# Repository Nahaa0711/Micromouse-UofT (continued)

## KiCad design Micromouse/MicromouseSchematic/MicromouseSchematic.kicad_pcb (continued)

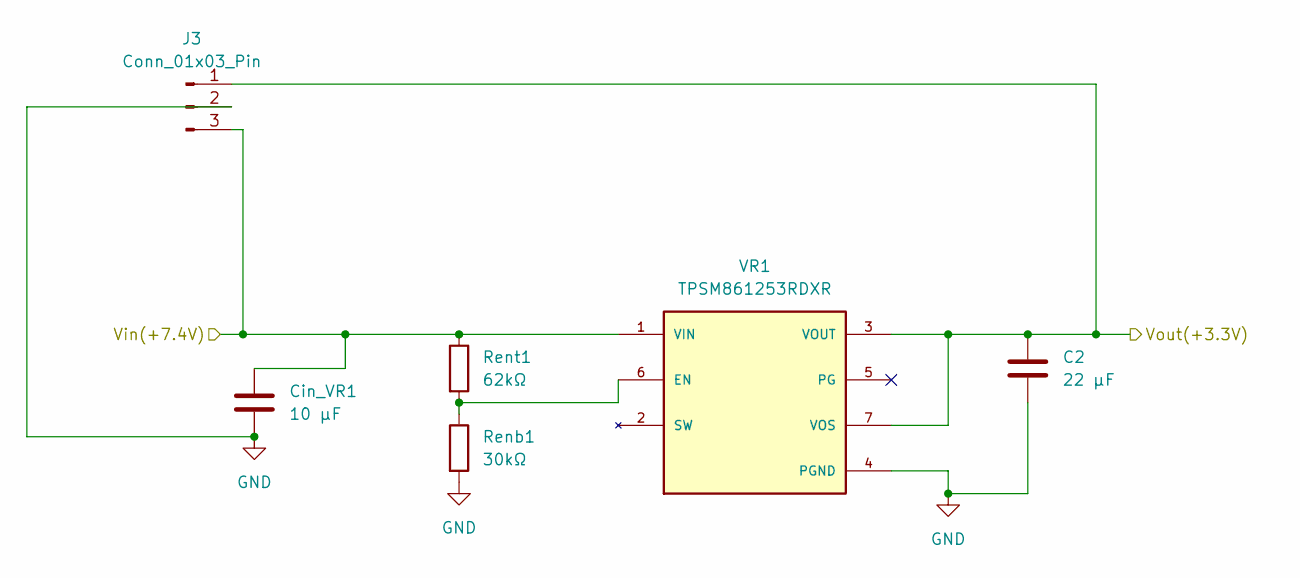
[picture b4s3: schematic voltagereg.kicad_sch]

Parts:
C2: 22 µF; C_0402_1005Metric
Cin_VR1: 10 µF; C_0402_1005Metric
J3: Conn_01x03_Pin; JST_ZH_B3B-ZR_1x03_P1.50mm_Vertical
Renb1: 30kΩ; R_0603_1608Metric
Rent1: 62kΩ; R_0603_1608Metric
VR1: TPSM861253RDXR; PARTREV B

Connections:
+3.3V: C2.1, J3.1, VR1.3 (VOUT), VR1.7 (VOS), VR1.14, VR1.15, VR1.16, VR1.17, VR1.18, VR1.19; also elsewhere on the board
+7.4V: Cin_VR1.1, J3.3, Rent1.1, VR1.1 (VIN); also elsewhere on the board
GND: C2.2, Cin_VR1.2, J3.2, Renb1.2, VR1.4 (PGND); also elsewhere on the board
unnamed: Renb1.1, Rent1.2, VR1.6 (EN)

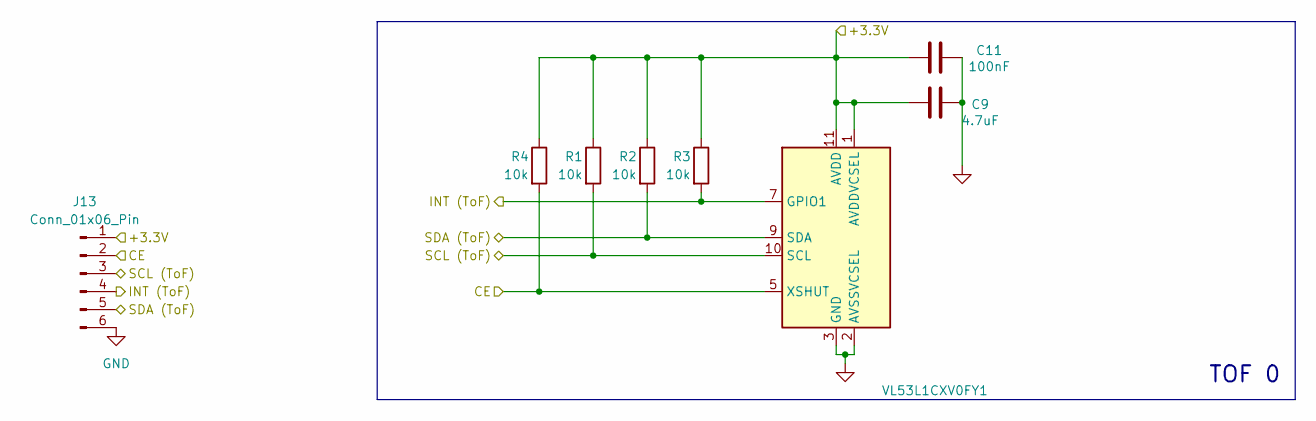
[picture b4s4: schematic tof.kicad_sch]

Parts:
C9: 4.7uF; C_0402_1005Metric
C11: 100nF; C_0402_1005Metric
J13: Conn_01x06_Pin; JST_ZH_B6B-ZR_1x06_P1.50mm_Vertical
R1, R2, R3, R4: 10k; R_0603_1608Metric
U1: VL53L1CXV0FY1; LGA12_STM

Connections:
+3.3V: C9.1, C11.1, J13.1, R1.1, R2.1, R3.1, R4.1, U1.1 (AVDDVCSEL), U1.11 (AVDD); also elsewhere on the board
GND: C9.2, C11.2, J13.6, U1.2 (AVSSVCSEL), U1.3 (GND), U1.4 (GND), U1.6 (GND), U1.12 (GND); also elsewhere on the board
I2C_SCL: J13.3, R1.2, U1.10 (SCL); also elsewhere on the board
I2C_SDA: J13.5, R2.2, U1.9 (SDA); also elsewhere on the board
TOF_CE: J13.2, R4.2, U1.5 (XSHUT); also elsewhere on the board
TOF_INT: J13.4, R3.2, U1.7 (GPIO1); also elsewhere on the board

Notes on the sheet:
TOF 0

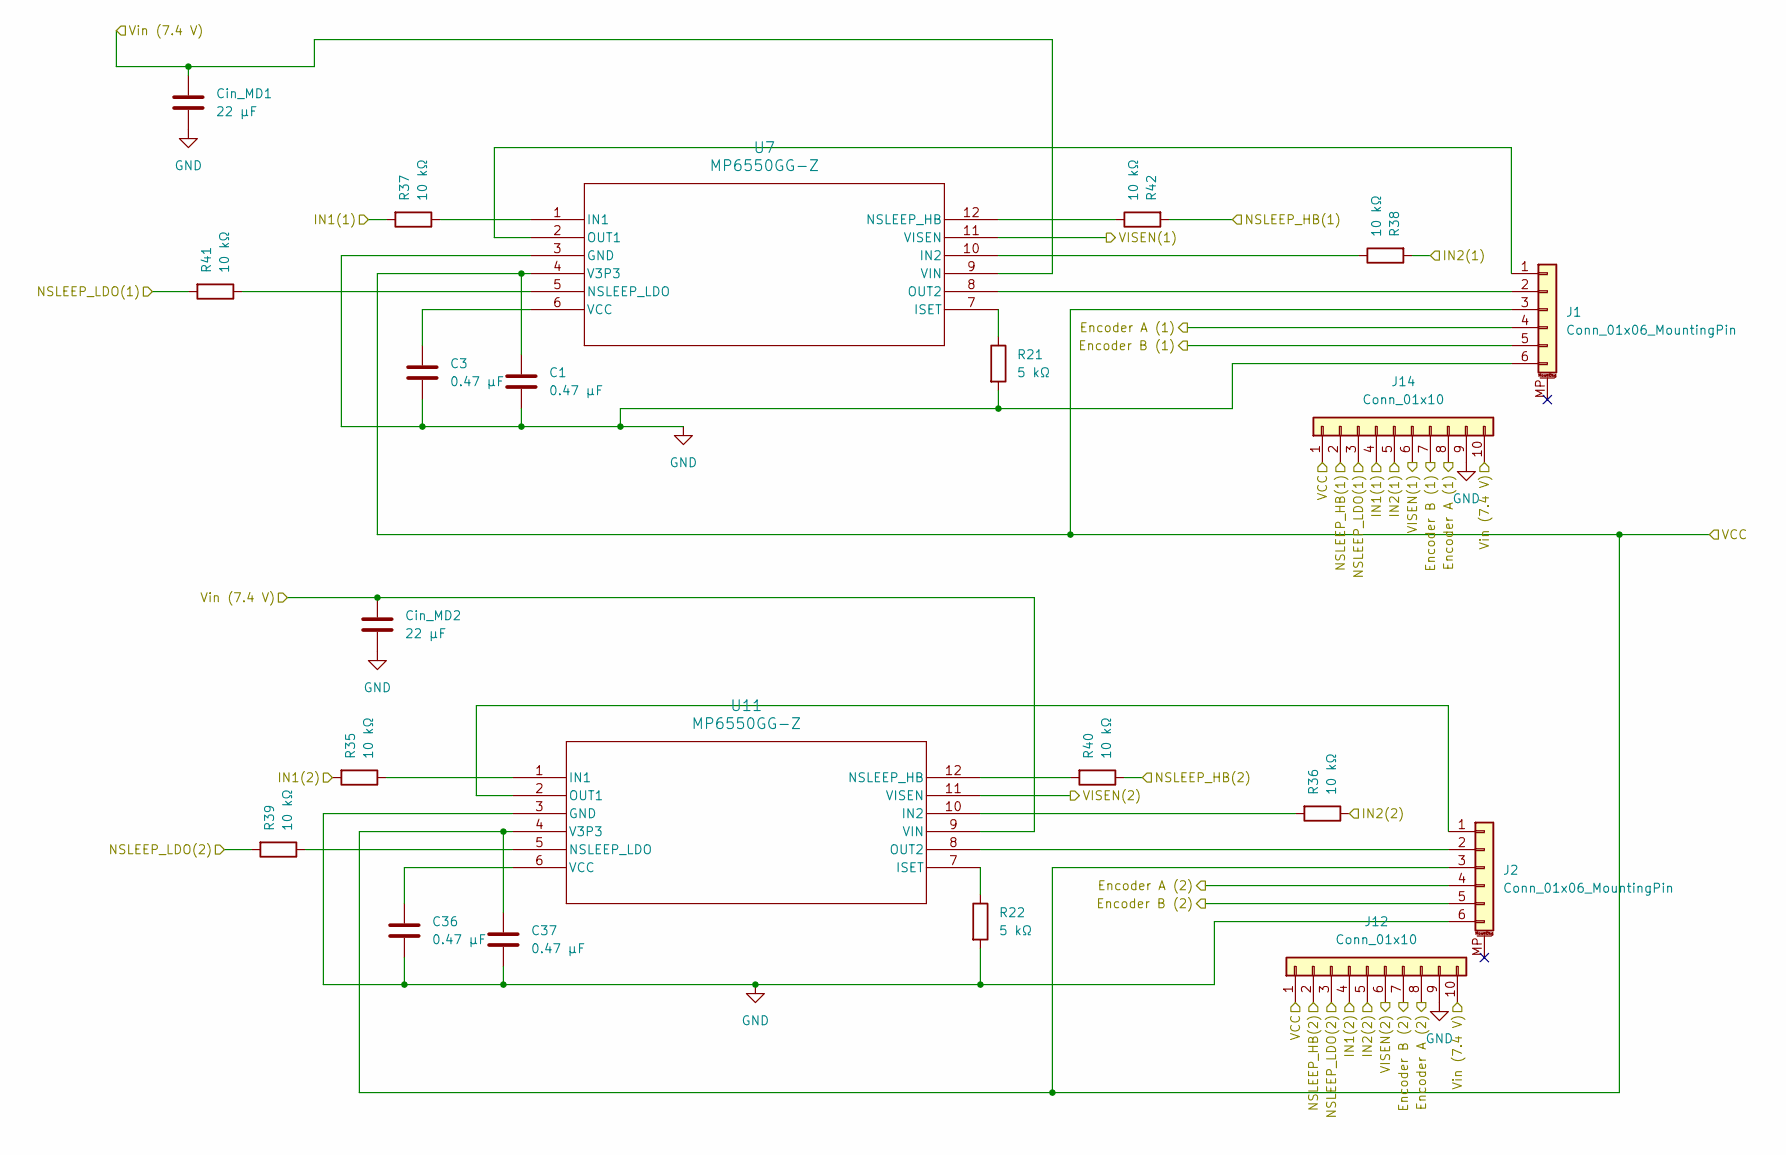
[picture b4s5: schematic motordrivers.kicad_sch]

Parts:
C1: 0.47 μF; C_0201_0603Metric
C3, C36, C37: 0.47 μF; C_0402_1005Metric
Cin_MD1, Cin_MD2: 22 μF; C_0402_1005Metric
J1, J2: Conn_01x06_MountingPin; JST_PH_B6B-PH-K_1x06_P2.00mm_Vertical
J12, J14: Conn_01x10; JST_ZH_B10B-ZR_1x10_P1.50mm_Vertical
R21, R22: 5 kΩ; R_0805_2012Metric
R35, R36, R37, R38, R39, R40, R41, R42: 10 kΩ; R_0603_1608Metric
U7, U11: MP6550GG-Z; MP6550_MNP

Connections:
+3.3V: C1.1, C37.1, J1.3, J2.3, J12.1, J14.1, U7.4 (V3P3), U11.4 (V3P3); also elsewhere on the board
+7.4V: Cin_MD1.1, Cin_MD2.1, J12.10, J14.10, U7.9 (VIN), U11.9 (VIN); also elsewhere on the board
Encoder_A_1: J1.4, J14.8; also elsewhere on the board
Encoder_A_2: J2.4, J12.8; also elsewhere on the board
Encoder_B_1: J1.5, J14.7; also elsewhere on the board
Encoder_B_2: J2.5, J12.7; also elsewhere on the board
GND: C1.2, C3.2, C36.2, C37.2, Cin_MD1.2, Cin_MD2.2, J1.6, J2.6, J12.9, J14.9, R21.2, R22.2, U7.3 (GND), U11.3 (GND); also elsewhere on the board
MO1_IN1: J14.4, R37.2; also elsewhere on the board
MO1_IN2: J14.5, R38.2; also elsewhere on the board
MO2_IN1: J12.4, R35.2; also elsewhere on the board
MO2_IN2: J12.5, R36.1; also elsewhere on the board
NSLEEP_HB_1: J14.2, R42.2; also elsewhere on the board
NSLEEP_HB_2: J12.2, R40.1; also elsewhere on the board
NSLEEP_LDO_1: J14.3, R41.2; also elsewhere on the board
NSLEEP_LDO_2: J12.3, R39.2; also elsewhere on the board
unnamed: J1.1, U7.2 (OUT1)
unnamed: J1.2, U7.8 (OUT2)
unnamed: J2.1, U11.2 (OUT1)
unnamed: J2.2, U11.8 (OUT2)
unnamed: R37.1, U7.1 (IN1)
unnamed: R38.1, U7.10 (IN2)
unnamed: R21.1, U7.7 (ISET)
unnamed: R42.1, U7.12 (NSLEEP_HB)
unnamed: R41.1, U7.5 (NSLEEP_LDO)
unnamed: C3.1, U7.6 (VCC)
unnamed: R35.1, U11.1 (IN1)
unnamed: R36.2, U11.10 (IN2)
unnamed: R22.1, U11.7 (ISET)
unnamed: R40.2, U11.12 (NSLEEP_HB)
unnamed: R39.1, U11.5 (NSLEEP_LDO)
unnamed: C36.1, U11.6 (VCC)
VISEN_1: J14.6, U7.11 (VISEN); also elsewhere on the board
VISEN_2: J12.6, U11.11 (VISEN); also elsewhere on the board

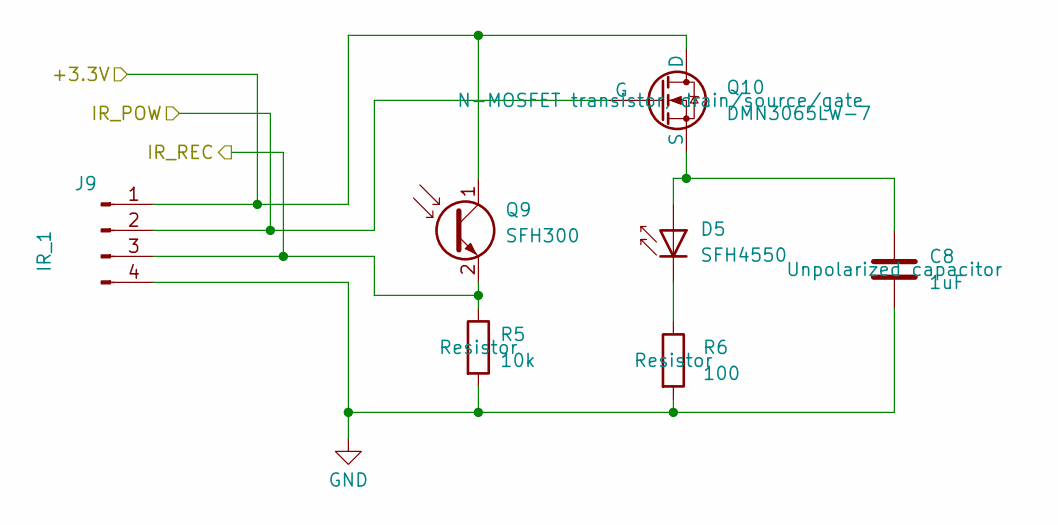
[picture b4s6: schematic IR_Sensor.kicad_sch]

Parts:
C8: 1uF; C_0402_1005Metric
D5: SFH4550; LED_D5.0mm_IRGrey
J9: IR_1; JST_ZH_B4B-ZR_1x04_P1.50mm_Vertical
Q9: SFH300; LED_D5.0mm_Clear
Q10: DMN3065LW-7
R5: 10k; R_0603_1608Metric
R6: 100; R_0603_1608Metric

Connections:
+3.3V: J9.1, Q9.1 (C), Q10.1 (D); also elsewhere on the board
GND: C8.2, J9.4, R5.2, R6.2; also elsewhere on the board
IR_POW_1: J9.2, Q10.2 (G); also elsewhere on the board
IR_REC_1: J9.3, Q9.2 (E), R5.1; also elsewhere on the board
unnamed: C8.1, D5.2 (A), Q10.3 (S)
unnamed: D5.1 (K), R6.1

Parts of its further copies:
C10, C12, C13: 1uF; C_0402_1005Metric
D1, D2, D3: SFH4550; LED_D5.0mm_IRGrey
J6, J7, J8: IR_1; JST_ZH_B4B-ZR_1x04_P1.50mm_Vertical
Q1, Q3, Q5: SFH300; LED_D5.0mm_Clear
Q2, Q4, Q6: DMN3065LW-7
R7, R9, R11: 10k; R_0603_1608Metric
R8, R10, R12: 100; R_0603_1608Metric

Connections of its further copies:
+3.3V: J6.1, J7.1, J8.1, Q1.1 (C), Q2.1 (D), Q3.1 (C), Q4.1 (D), Q5.1 (C), Q6.1 (D); also elsewhere on the board
GND: C10.2, C12.2, C13.2, J6.4, J7.4, J8.4, R7.2, R8.2, R9.2, R10.2, R11.2, R12.2; also elsewhere on the board
IR_POW_2: J6.2, Q2.2 (G); also elsewhere on the board
IR_POW_3: J7.2, Q4.2 (G); also elsewhere on the board
IR_POW_4: J8.2, Q6.2 (G); also elsewhere on the board
IR_REC_2: J6.3, Q1.2 (E), R7.1; also elsewhere on the board
IR_REC_3: J7.3, Q3.2 (E), R9.1; also elsewhere on the board
IR_REC_4: J8.3, Q5.2 (E), R11.1; also elsewhere on the board
unnamed: C10.1, D1.2 (A), Q2.3 (S)
unnamed: D1.1 (K), R8.1
unnamed: C12.1, D2.2 (A), Q4.3 (S)
unnamed: D2.1 (K), R10.1
unnamed: C13.1, D3.2 (A), Q6.3 (S)
unnamed: D3.1 (K), R12.1

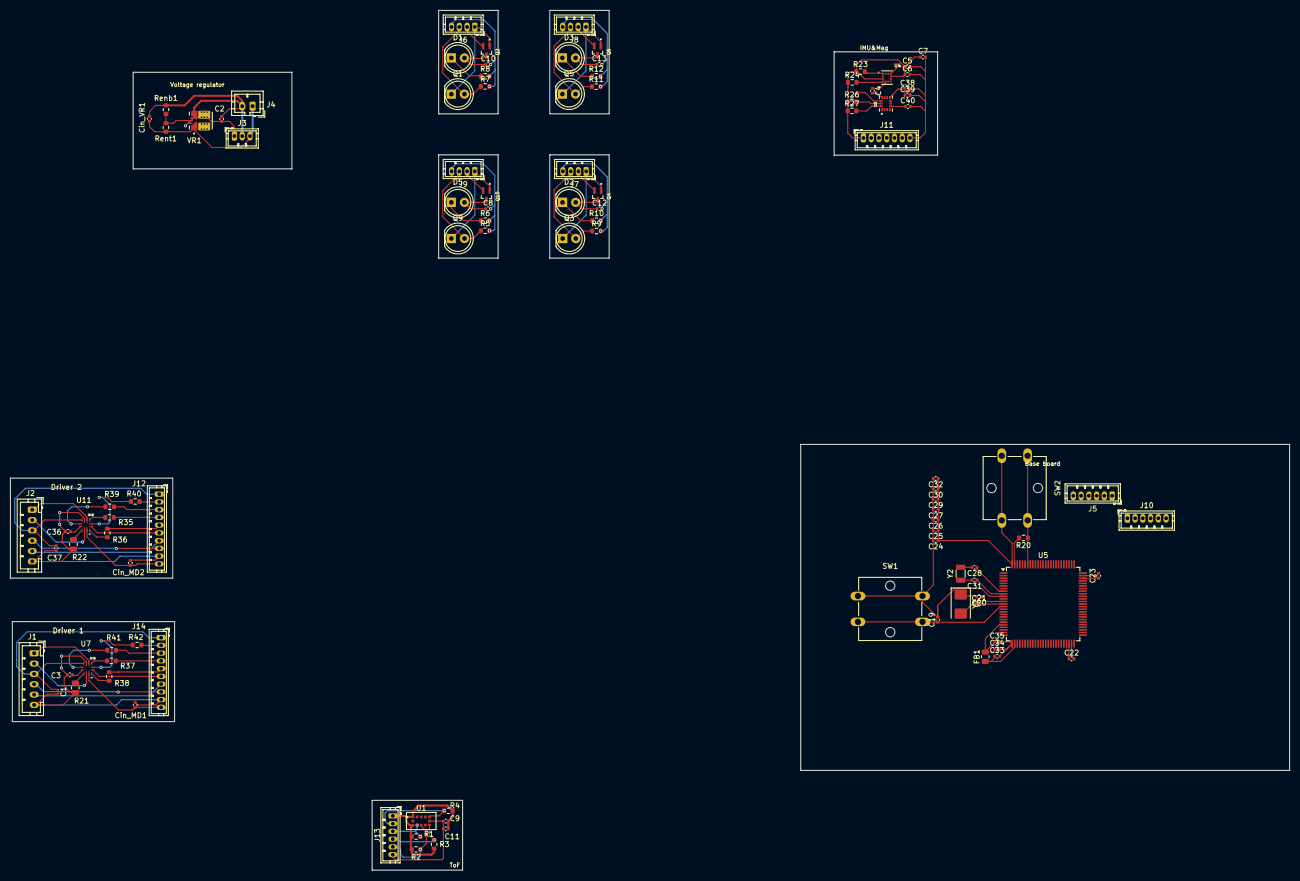
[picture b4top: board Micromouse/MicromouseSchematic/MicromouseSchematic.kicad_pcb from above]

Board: 2 copper layers, 247.6 x 166.4 mm, 105 parts (0 on the bottom side), 78 nets.

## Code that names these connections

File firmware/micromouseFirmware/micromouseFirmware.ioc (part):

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Mcu.Name=STM32F746VETx
Mcu.Package=LQFP100
Mcu.UserName=STM32F746VETx
PA10.Mode=Asynchronous
PA10.Signal=USART1_RX
PA13.Mode=Serial_Wire
PA13.Signal=SYS_JTMS-SWDIO
PA14.Mode=Serial_Wire
PA14.Signal=SYS_JTCK-SWCLK
PA2.GPIOParameters=GPIO_Label
PA2.GPIO_Label=VISEN_1
PA2.Signal=ADCx_IN2
PA3.GPIOParameters=GPIO_Label
PA3.GPIO_Label=VISEN_2
PA3.Signal=ADCx_IN3
PA6.GPIOParameters=GPIO_Label
PA6.GPIO_Label=Encoder_A_2
PA6.Signal=S_TIM3_CH1
PA7.GPIOParameters=GPIO_Label
PA7.GPIO_Label=Encoder_B_2
PA7.Signal=S_TIM3_CH2
PA9.Mode=Asynchronous
PA9.Signal=USART1_TX
PB0.Signal=GPIO_Output
PB4.GPIOParameters=GPIO_Label
PB4.GPIO_Label=BT_EN
PB4.Signal=GPIO_Input
PB5.GPIOParameters=GPIO_Label
PB5.GPIO_Label=BT_STATE
PB5.Signal=GPIO_Input
PC14/OSC32_IN.Mode=LSE-External-Oscillator
PC14/OSC32_IN.Signal=RCC_OSC32_IN
PC15/OSC32_OUT.Mode=LSE-External-Oscillator
PC15/OSC32_OUT.Signal=RCC_OSC32_OUT
PD12.GPIOParameters=GPIO_Label
PD12.GPIO_Label=MO1_IN1
PD12.Signal=S_TIM4_CH1
PD13.GPIOParameters=GPIO_Label
PD13.GPIO_Label=MO1_IN2
PD13.Signal=S_TIM4_CH2
PD14.GPIOParameters=GPIO_Label
PD14.GPIO_Label=MO2_IN1
PD14.Signal=S_TIM4_CH3
PD15.GPIOParameters=GPIO_Label
PD15.GPIO_Label=MO2_IN2
PD15.Signal=S_TIM4_CH4
PE10.GPIOParameters=GPIO_Label
PE10.GPIO_Label=NSLEEP_HB_2
PE10.Signal=GPIO_Output
PE11.GPIOParameters=GPIO_Label
PE11.GPIO_Label=Encoder_B_1
PE11.Signal=S_TIM1_CH2
PE7.GPIOParameters=GPIO_Label
PE7.GPIO_Label=NSLEEP_HB_1
PE7.Signal=GPIO_Output
PE9.GPIOParameters=GPIO_Label
PE9.GPIO_Label=Encoder_A_1
PE9.Signal=S_TIM1_CH1
PH0/OSC_IN.Mode=HSE-External-Oscillator
PH0/OSC_IN.Signal=RCC_OSC_IN
PH1/OSC_OUT.Mode=HSE-External-Oscillator
PH1/OSC_OUT.Signal=RCC_OSC_OUT
RCC.HSE_VALUE=8000000
RCC.SYSCLKFreq_VALUE=8000000
RCC.SYSCLKSource=RCC_SYSCLKSOURCE_HSE
board=custom

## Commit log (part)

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2025-06-22 Documentation Obsidian Push
2025-07-04 Added KB/MazeAlgorithm, starter links set, continue making pages
2025-07-13 Writing the Recipe so we can cook
2025-07-13 +1 cheese
2025-07-13 updated stuff
2025-07-13 added backlog items
2025-07-13 Added Workshops
2025-07-13 aofbafafaeF
2025-07-13 Added Git Ignore
2025-07-13 test change
2025-07-17 moved file
2025-07-23 updated github info
2025-07-23 updated git instructions
2025-07-23 aofnafa
2025-07-28 27/07 Meeting
2025-08-01 added some exampple designs
2025-08-01 updated brainstorming
2025-08-14 merge
2025-10-28 Added micromouse master schematic template in ./Micromouse
2025-10-28 I lied before, here are the schematics
2025-10-31 tof version 1
2025-11-08 random changes
2025-11-08 chore: old meeting notes
2025-11-08 updated gitignore
2025-11-08 whatever
2025-11-08 afnaf
2025-11-08 Added microcontroller schematics
2025-11-15 changed motor driver schematics
2025-11-15 Changed net labels
2025-11-15 Updated IMU and Magnetometer schematics
2025-11-15 Made changesto IMU/magnetometer
2025-11-16 Added IR, programming header, i2c & timer pins
2025-11-22 added some stuff
2025-11-22 afoiaybf;a4'4f
2026-04-02 Micromouse KiCad: MP6550 libs in project, fp-lib paths, schematic updates
    Move MP6550G-Z symbol and legacy footprints into MicromouseSchematic, add
    MP6550G-Z.pretty with MP6550_MNP footprint, and point fp-lib-table at the
    project-local MM_MP6550G-Z library.
    Replace old absolute footprint paths with this repo’s Micromouse tree and
    MM_* library names. Update root schematic and IMU/IR/motor/TOF/regulator
    subsheets; add empty bluethooth.kicad_sch hierarchical sheet. Extend KiCad
2026-04-09 Micromouse KiCad: STM32-centric routing; ERC errors 23→6; backups and gitignore
    Body:
    Connected almost all STM32 signals; ERC down to 6
    Rework root schematic plus motor driver, IMU/magnetometer, IR sensor, and TOF
    subsheets so the bulk of signals reach the STM32. KiCad ERC is not fully clean
    yet, but major nets are in place: errors dropped from 23 to 6 while many
    previously unconnected signals were wired.
2026-04-12 Micromouse KiCad: MP6550 layout, schematic updates; ERC clean, warnings ~5–6
    Relocate MP6550G-Z symbol and footprint trees from MicromouseSchematic into
    Micromouse/MP6550G-Z and refresh sym-lib-table (portable ${KIPRJMOD} paths
    where applicable, MP6550 at new location).
    Update root schematic plus IMU, IR, motor driver, and TOF subsheets. KiCad
    ERC: all errors resolved (previously 6 remaining after earlier bring-up).
    Warnings reduced from roughly 35–40+ down to about 5–6.
2026-04-18 updated git ignore
2026-04-18 fix: footprint errors and add setup guide
2026-04-18 fixed sym erc violation
2026-04-18 arnafraf
2026-04-18 aornfaFE
2026-04-18 udpated programming header
2026-04-22 assigned capacitor footprints. still have to figure out rest
2026-04-22 added resistors, must need to add capacitors
2026-04-25 Changd IR sensors and emmiters to 5mm LEDs
2026-04-25 Cleared all footprint errors and issues. Updated crystal caps to match Cload
2026-04-25 Micromouse KiCad: VL53L4 TOF footprint/sym; fp-lib via KICAD_ADDITIONAL_FOOTPRINT
    Add UltraLibrarian VL53L4CDV0DH-1 KiCad symbol and LGA12_STM footprint plus
    vendor readme; register them in sym-lib-table and fp-lib-table.
    Point MM footprint libraries at ${KICAD_ADDITIONAL_FOOTPRINT}/... for
    portable paths; add MM_VL53L4CDV0DH-1.
    Rework tof.kicad_sch (large cleanup vs embedded library bulk) and touch root
    MicromouseSchematic.kicad_sch and MicromouseSchematic.kicad_pro for project
2026-04-29 added resistors
2026-04-30 Schematics clear, moved all footprints to pcb and voltage regulator completed. The layout begins
2026-04-30 git ignore
2026-04-30 to-do IMU+Mag figure it out or mutli layer pcb?
2026-05-02 added ir sensors stuff
2026-05-02 Afarnfa
2026-05-02 Add ToF sensor connector (J13) to schematic and did TOF PCB layout
2026-05-02 Completed motor driver layout
2026-05-11 Fixed the rasnet issue and back copper layer issue
2026-05-16 updated base pcd area, attached crystal oscillators and ferite bead - must still figure out config for the connectors
